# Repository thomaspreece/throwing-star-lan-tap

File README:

# Lan Tap
This repo contains the modified version of the Throwing Star LAN TAP to use the generic RJ45 connectors I bought from Ebay.

## Original README

Throwing Star LAN TAP
Copyright 2011 Michael Ossmann <mike@ossmann.com>
These design files are licensed under the terms in the file, COPYING.

parts required:
qty 4 RJ45 connectors: Amphenol RJHSE-5080 (unshielded) or RJHSE-5380 (shielded)
qty 2 220pF through-hole capacitors with .1" lead spacing (e.g. Xicon 140-50P2-221K-RC)

For more information: http://greatscottgadgets.com/

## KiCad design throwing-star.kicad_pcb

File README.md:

# Lan Tap
This repo contains the modified version of the Throwing Star LAN TAP to use the generic RJ45 connectors I bought from Ebay.

## Original README

Throwing Star LAN TAP
Copyright 2011 Michael Ossmann <mike@ossmann.com>
These design files are licensed under the terms in the file, COPYING.

parts required:
qty 4 RJ45 connectors: Amphenol RJHSE-5080 (unshielded) or RJHSE-5380 (shielded)
qty 2 220pF through-hole capacitors with .1" lead spacing (e.g. Xicon 140-50P2-221K-RC)

For more information: http://greatscottgadgets.com/

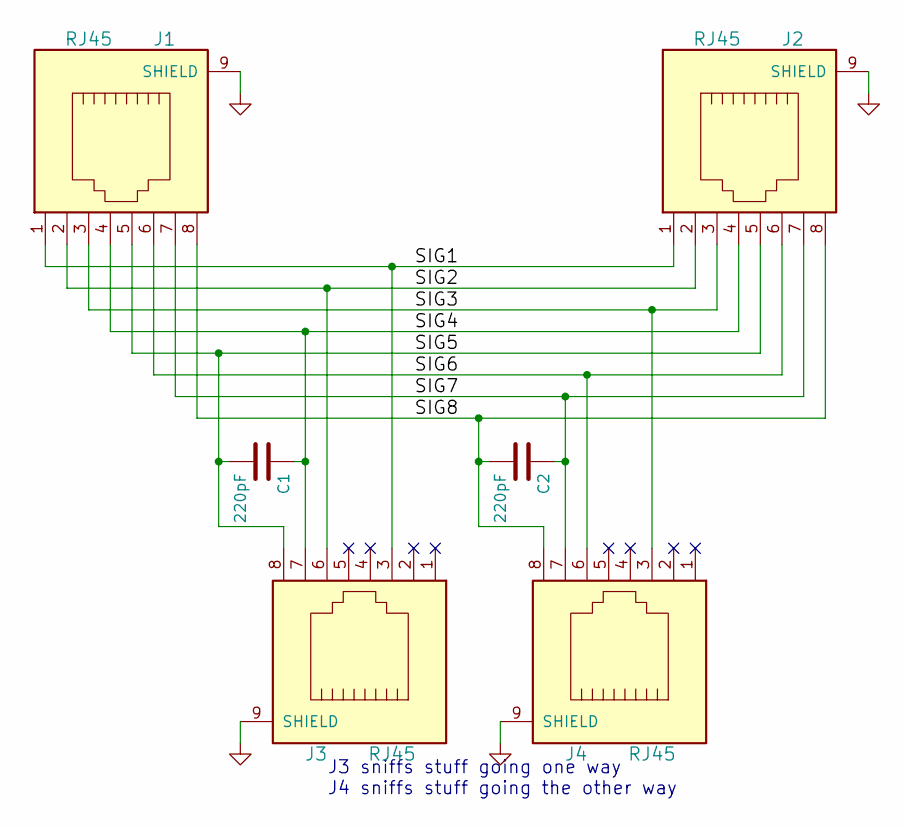
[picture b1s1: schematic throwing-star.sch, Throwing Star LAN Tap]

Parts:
C1, C2: 220pF; C_Disc_D3.8mm_W2.6mm_P2.50mm
J1, J2, J3, J4: RJ45

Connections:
/SIG1: J1.1, J2.1, J3.3
/SIG2: J1.2, J2.2, J3.6
/SIG3: J1.3, J2.3, J4.3
/SIG4: C1.1, J1.4, J2.4, J3.7
/SIG5: C1.2, J1.5, J2.5, J3.8
/SIG6: J1.6, J2.6, J4.6
/SIG7: C2.1, J1.7, J2.7, J4.7
/SIG8: C2.2, J1.8, J2.8, J4.8
GND: J1.9 (SHIELD), J2.9 (SHIELD), J3.9 (SHIELD), J4.9 (SHIELD)

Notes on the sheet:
J3 sniffs stuff going one way J4 sniffs stuff going the other way

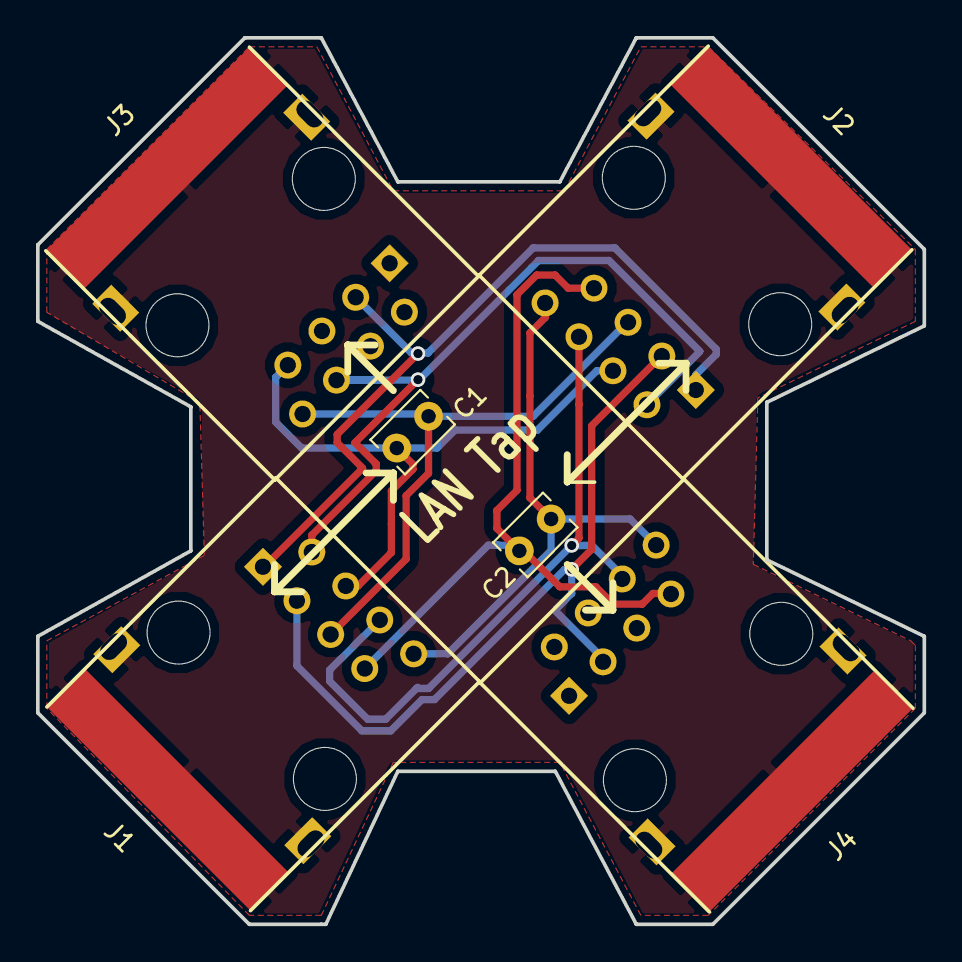
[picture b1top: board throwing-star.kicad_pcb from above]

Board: 2 copper layers, 49.2 x 49.2 mm, 6 parts (0 on the bottom side), 9 nets.

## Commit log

2021-05-01 fix readme
2022-08-22 fix: add image

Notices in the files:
throwing-star.sch:
Copyright 2010 Michael Ossmann, Great Scott Gadgets
License: GPL v2
